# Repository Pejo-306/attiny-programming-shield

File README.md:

# ATTiny programming shield (using an Arduino Uno)

This project is a simple PCB design which can be used to program an
ATTiny(25/45/85) with an Arduino Uno as an ISP.

# Getting started

## Required parts
The following is a list of the parts used in this project:

* DIP 8-pin socket
* 10uF electrolytic capacitor
* Male pin headers 2.54mm pitch
  * 01x10 (1 piece)
  * 01x08 (1 piece)
* LED 5mm (optional)
* 220 ohm resistor (optional)
* Arduino Uno board
* ATTiny(25/45/85)

_Note_: all components use THT

The listed LED and resistor are optional and can be used as indication that the
Arduino is providing 5V power to the circuit.

## Assembling the board
After gathering the required parts, you can either order the PCB from your
favorite PCB manufacturer or create the PCB yourself. The circuit can also
be assembled on a breadboard with relative ease.

## Programming the ATTiny
You must first upload the example ISP sketch to the Arduino Uno 
(in the Arduino IDE: "File -> Examples -> 11.Arduino ISP -> Arduino ISP").
Afterwards, place both the Arduino Uno board and the ATTiny on the PCB.

You will need ATTiny board definitions for the Arduino IDE. The ones I
recommend (and use) are those by Spence Konde in his ATTinyCore github project
(link below). Other board definitions can also be used but you must research them
on your own.

After you have obtained the required board definitions, select the appropriate
one (i.e. ATTiny(25/45/85)) from the "Tools -> Board" menu in the Arduino IDE.
Select the port ("Tools -> Port") where the Arduino is connected. Under the 
"Tools -> Programmer" menu choose "Arduino as ISP". Afterwards, write your code
and upload it. If all goes well, then your ATTiny should be executing your
uploaded program.

_Note_: different ATTiny board definitions may have specific requirements
(such as the suggested ATTinyCore ones). Refer to your chosen board
definitions' documentation for more details.

## Using the ATTiny
If your code has successfully been uploaded to the ATTiny chip, you should be
able to take it out of the IC socket and use it in your other projects.

_Note_: the ATTiny does not support all of the functionality that the
Arduino boards provide. You must research/experiment to find out what works
and what does not.

# Acknowledgments

* [ATTinyCore](https://github.com/SpenceKonde/ATTinyCore)
by Spence Konde - suggested Arduino IDE board definitions for ATTiny chips
* [GreatScott's YouTube video on the topic](https://www.youtube.com/watch?v=9LjfkjwMqXI&t=186s) - 
inspiration for this project

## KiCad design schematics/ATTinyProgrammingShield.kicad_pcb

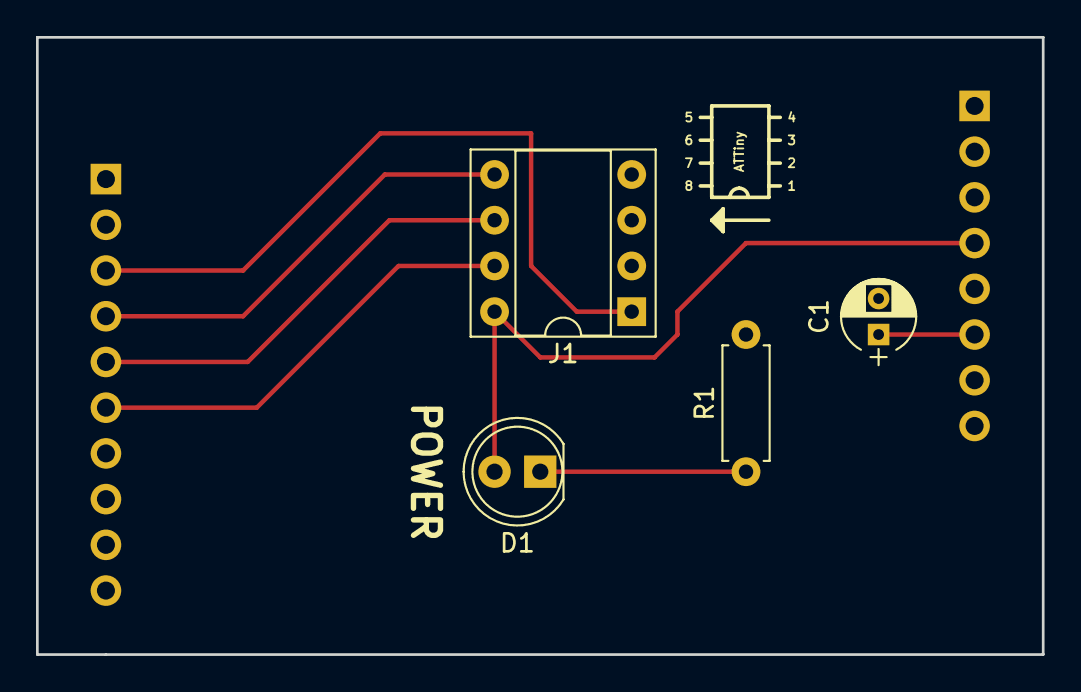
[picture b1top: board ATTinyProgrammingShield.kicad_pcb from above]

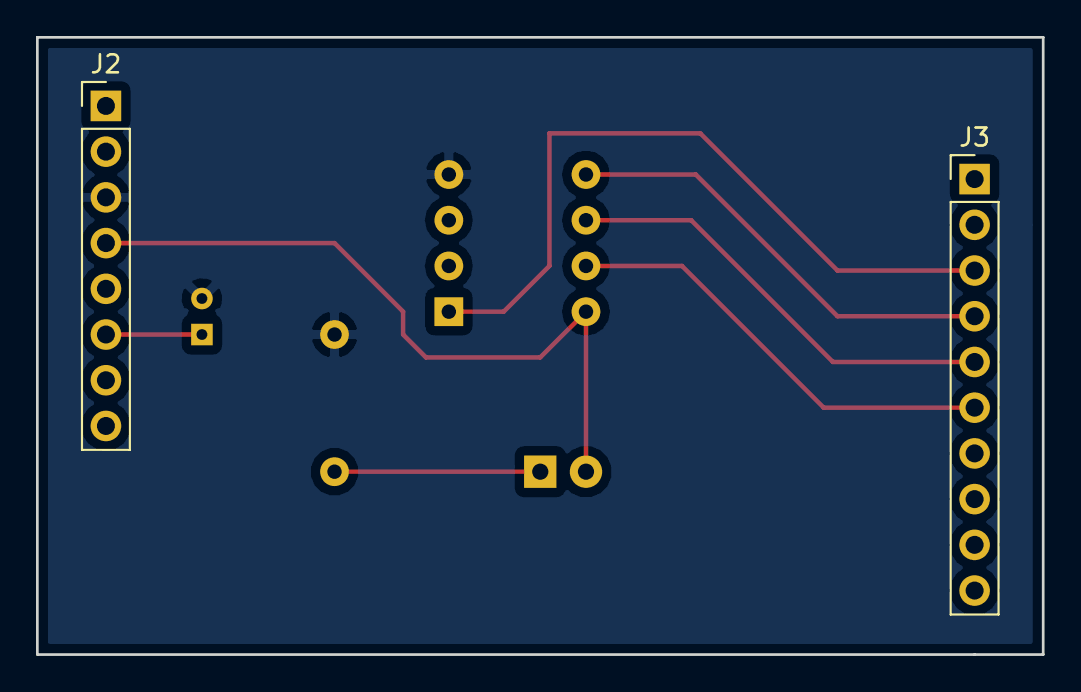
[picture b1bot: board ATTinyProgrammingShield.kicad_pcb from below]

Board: 2 copper layers, 55.9 x 34.3 mm, 6 parts (2 on the bottom side), 8 nets.

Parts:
C1: 10uF; CP_Radial_D4.0mm_P2.00mm
D1: LED; LED_D5.0mm
J1: DIP8_Socket; DIP-8_W7.62mm_Socket
J2: Conn_01x08_Male; Pin_Header_Straight_1x08_Pitch2.54mm
J3: Conn_01x10_Male; Pin_Header_Straight_1x10_Pitch2.54mm
R1: 220; R_Axial_DIN0207_L6.3mm_D2.5mm_P7.62mm_Horizontal

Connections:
+5V: D1.2, J1.8, J2.4
/RESET: C1.1, J2.6
/a1: J1.1, J3.3
/a5: J1.5, J3.4
/a6: J1.6, J3.5
/a7: J1.7, J3.6
Earth: C1.2, J1.4, J2.3, R1.2
unnamed: D1.1, R1.1

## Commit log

2018-07-22 Create LICENSE
2018-07-22 Initial commit. Commit schematics
2018-07-22 Add LED power indicator. Associate components with footprints
2018-07-22 Design an appropriate PCB
2018-07-22 Add proper README
2018-07-31 Update to KiCad 5 from KiCad 4
    - use KiCad's standard library Arduino shield symbol and footprint
    - ground the second copper layer of the PCB (and consequently unground
    the first copper layer of the PCB)
2018-08-07 Remove acknowledgment of Alarm Siren's Arduino KiCad library
    The Arduino schematic symbol and PCB footprint have been replaced
    by the standard KiCad 5.0 implementations.
